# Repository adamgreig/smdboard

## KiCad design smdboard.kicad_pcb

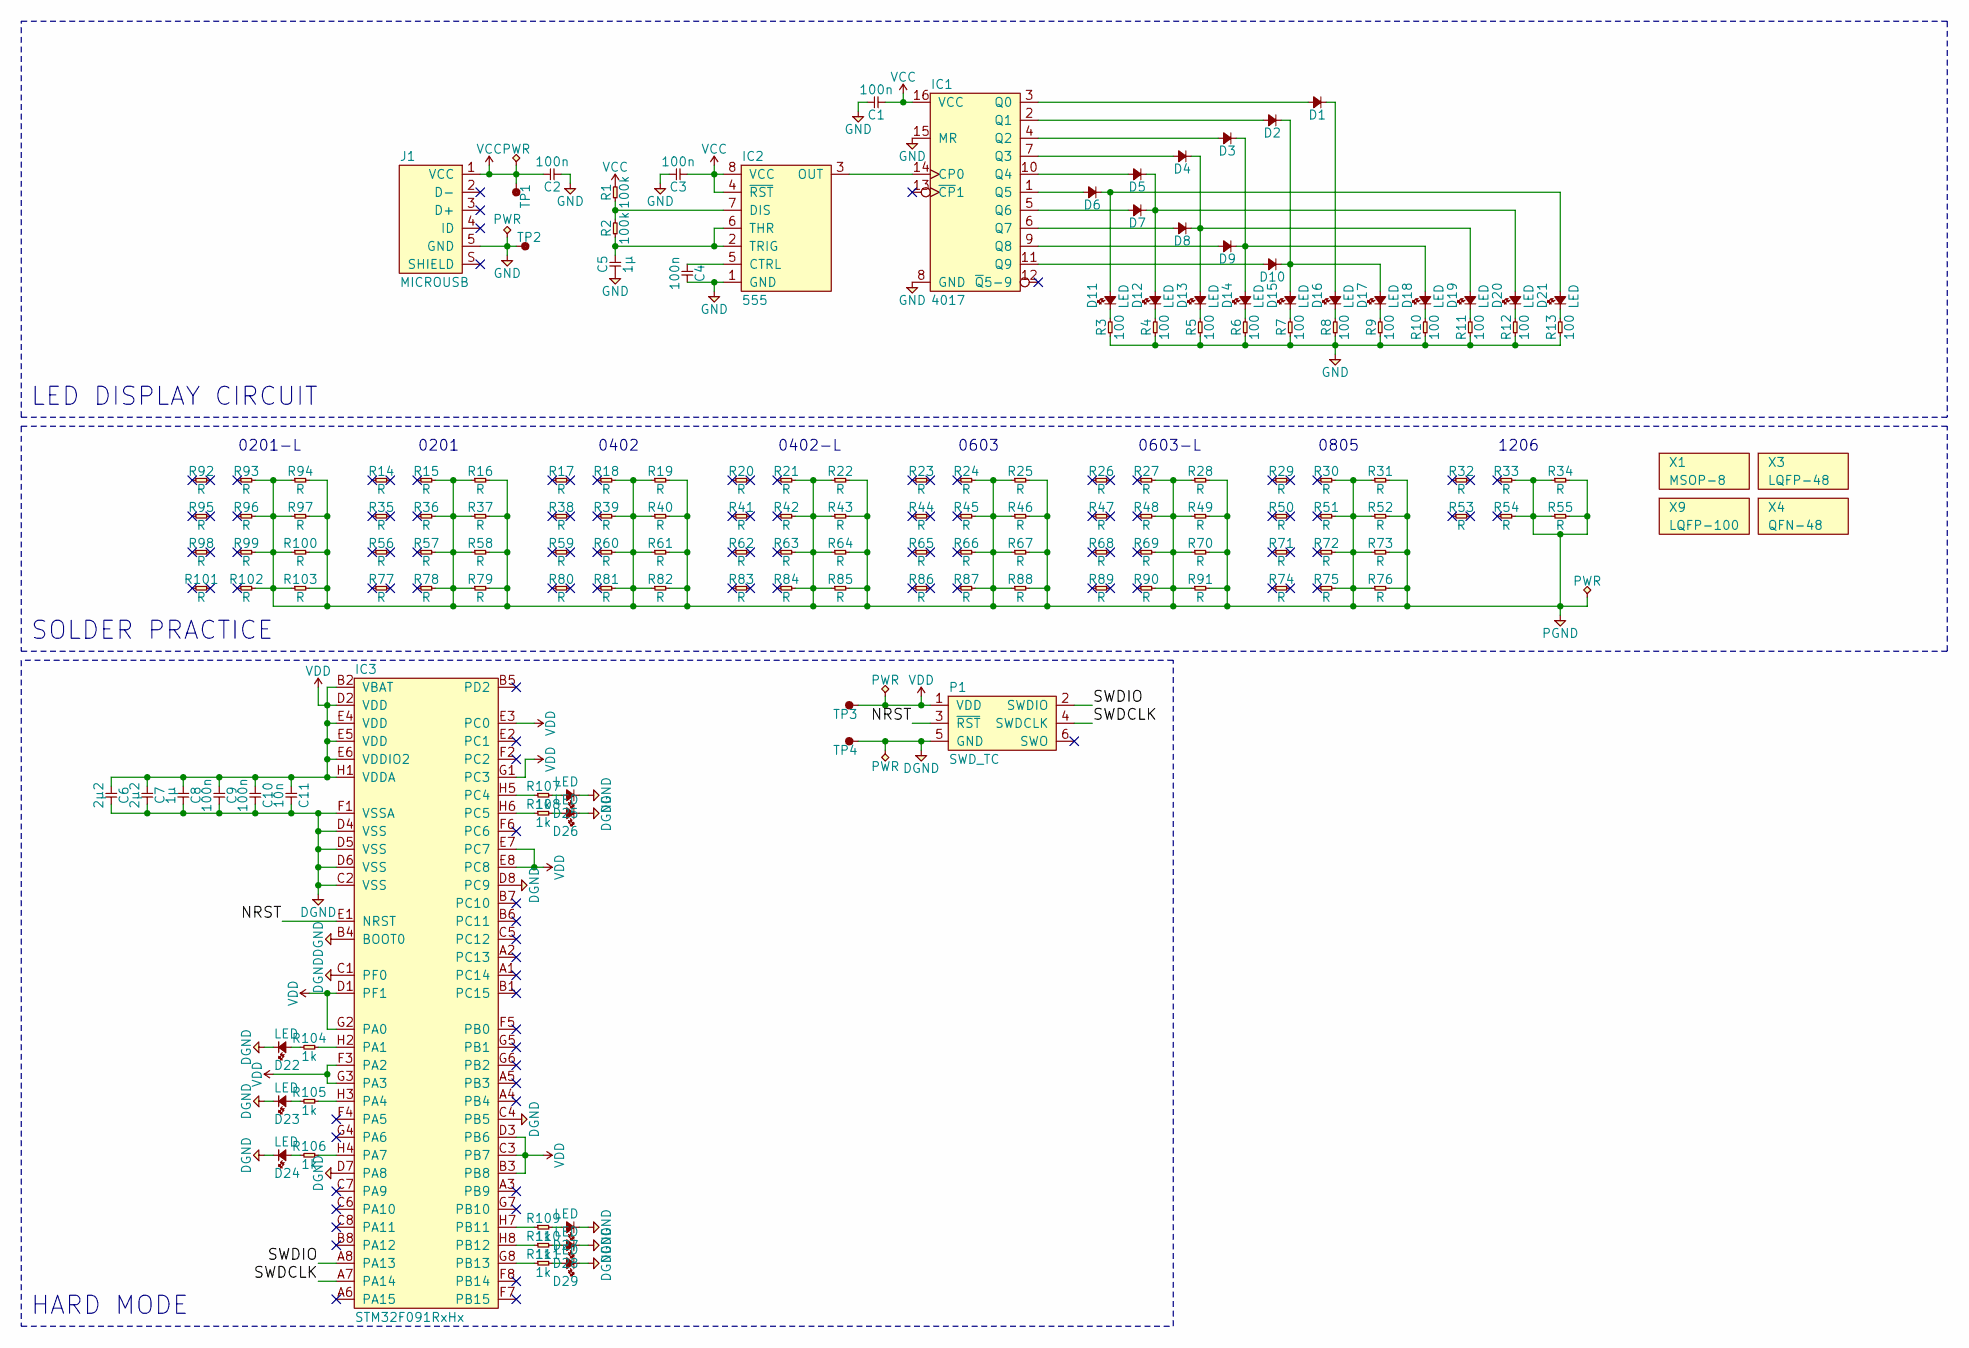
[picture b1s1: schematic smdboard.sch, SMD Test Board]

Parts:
C1, C2, C3, C4: 100n; 0805
C5: 1µ; 0805
C6, C7: 2µ2; 0603-L
C8: 1µ; 0603-L
C9, C10: 100n; 0402-L
C11: 10n; 0402-L
D1, D2, D3, D4, D5, D6, D7, D8, D9, D10: SOD-323; Farnell 1466524
D11, D12, D13, D14, D15, D16, D17, D18, D19, D20, D21: LED; 0805-LED
D22, D23, D24, D25, D26, D27, D28, D29: LED; 0603-LED
IC1: 4017; SOIC-16; Farnell 1085280
IC2: 555; SOIC-8; Farnell 9589880
IC3: STM32F091RxHx; UFBGA-64; Farnell 2503242
J1: MICROUSB; MICROUSB_MOLEX_47589-0001; Farnell 1568023
P1: SWD_TC; TC2030-NL
R1, R2: 100k; 0805
R3, R4, R5, R6, R7, R8, R9, R10, R11, R12, R13: 100; 0805
R14, R15, R16, R35, R36, R37, R56, R57, R58, R77, R78, R79: R; 0201
R17, R18, R19, R38, R39, R40, R59, R60, R61, R80, R81, R82: R; 0402
R20, R21, R22, R41, R42, R43, R62, R63, R64, R83, R84, R85: R; 0402-L
R23, R24, R25, R44, R45, R46, R65, R66, R67, R86, R87, R88: R; 0603
R26, R27, R28, R47, R48, R49, R68, R69, R70, R89, R90, R91: R; 0603-L
R29, R30, R31, R50, R51, R52, R71, R72, R73, R74, R75, R76: R; 0805
R32, R33, R34, R53, R54, R55: R; 1206
R92, R93, R94, R95, R96, R97, R98, R99, R100, R101, R102, R103: R; 0201-L
R104, R105, R106, R107, R108, R109, R110, R111: 1k; 0402-L
TP1, TP2, TP3, TP4: TESTPAD; WIREPAD
X1: MSOP-8
X3: LQFP-48
X4: QFN-48; QFN-48-EP-ST
X9: LQFP-100

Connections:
/NRST: IC3.E1 (NRST), P1.3 (~RST)
/SWDCLK: IC3.A7 (PA14), P1.4 (SWDCLK)
/SWDIO: IC3.A8 (PA13), P1.2 (SWDIO)
DGND: C6.2, C7.2, C8.2, C9.2, C10.2, C11.2, D22.1, D23.1, D24.1, D25.1, D26.1, D27.1, D28.1, D29.1, IC3.B4 (BOOT0), IC3.C1 (PF0), IC3.C2 (VSS), IC3.C4 (PB5), IC3.D4 (VSS), IC3.D5 (VSS), IC3.D6 (VSS), IC3.D7 (PA8), IC3.D8 (PC9), IC3.F1 (VSSA), P1.5 (GND), TP4.1
GND: C1.2, C2.1, C3.2, C4.2, C5.1, IC1.8 (GND), IC1.15 (MR), IC2.1 (GND), J1.5 (GND), R3.1, R4.1, R5.1, R6.1, R7.1, R8.1, R9.1, R10.1, R11.1, R12.1, R13.1, TP2.1
unnamed: C4.1, IC2.5 (CTRL)
unnamed: C5.2, IC2.2 (TRIG), IC2.6 (THR), R2.1
unnamed: D1.1, D16.2
unnamed: D1.2, IC1.3 (Q0)
unnamed: D2.2, IC1.2 (Q1)
unnamed: D3.2, IC1.4 (Q2)
unnamed: D4.2, IC1.7 (Q3)
unnamed: D5.2, IC1.10 (Q4)
unnamed: D6.2, IC1.1 (Q5)
unnamed: D7.2, IC1.5 (Q6)
unnamed: D8.2, IC1.6 (Q7)
unnamed: D9.2, IC1.9 (Q8)
unnamed: D2.1, D10.1, D15.2, D17.2
unnamed: D10.2, IC1.11 (Q9)
unnamed: D11.1, R3.2
unnamed: D6.1, D11.2, D21.2
unnamed: D12.1, R4.2
unnamed: D5.1, D7.1, D12.2, D20.2
unnamed: D13.1, R5.2
unnamed: D4.1, D8.1, D13.2, D19.2
unnamed: D14.1, R6.2
unnamed: D3.1, D9.1, D14.2, D18.2
unnamed: D15.1, R7.2
unnamed: D16.1, R8.2
unnamed: D17.1, R9.2
unnamed: D18.1, R10.2
unnamed: D19.1, R11.2
unnamed: D20.1, R12.2
unnamed: D21.1, R13.2
unnamed: D22.2, R104.2
unnamed: D23.2, R105.2
unnamed: D24.2, R106.2
unnamed: D25.2, R107.2
unnamed: D26.2, R108.2
unnamed: D27.2, R109.2
unnamed: D28.2, R110.2
unnamed: D29.2, R111.2
unnamed: IC1.14 (CP0), IC2.3 (OUT)
unnamed: IC2.7 (DIS), R1.1, R2.2
unnamed: IC3.G8 (PB13), R111.1
unnamed: IC3.H2 (PA1), R104.1
unnamed: IC3.H3 (PA4), R105.1
unnamed: IC3.H4 (PA7), R106.1
unnamed: IC3.H5 (PC4), R107.1
unnamed: IC3.H6 (PC5), R108.1
unnamed: IC3.H7 (PB11), R109.1
unnamed: IC3.H8 (PB12), R110.1
PGND: R15.2, R16.1, R16.2, R18.2, R19.1, R19.2, R21.2, R22.1, R22.2, R24.2, R25.1, R25.2, R27.2, R28.1, R28.2, R30.2, R31.1, R31.2, R33.2, R34.1, R34.2, R36.2, R37.1, R37.2, R39.2, R40.1, R40.2, R42.2, R43.1, R43.2, R45.2, R46.1, R46.2, R48.2, R49.1, R49.2, R51.2, R52.1, R52.2, R54.2, R55.1, R55.2, R57.2, R58.1, R58.2, R60.2, R61.1, R61.2, R63.2, R64.1, R64.2, R66.2, R67.1, R67.2, R69.2, R70.1, R70.2, R72.2, R73.1, R73.2, R75.2, R76.1, R76.2, R78.2, R79.1, R79.2, R81.2, R82.1, R82.2, R84.2, R85.1, R85.2, R87.2, R88.1, R88.2, R90.2, R91.1, R91.2, R93.2, R94.1, R94.2, R96.2, R97.1, R97.2, R99.2, R100.1, R100.2, R102.2, R103.1, R103.2
VCC: C1.1, C2.2, C3.1, IC1.16 (VCC), IC2.4 (~RST), IC2.8 (VCC), J1.1 (VCC), R1.2, TP1.1
VDD: C6.1, C7.1, C8.1, C9.1, C10.1, C11.1, IC3.B2 (VBAT), IC3.B3 (PB8), IC3.C3 (PB7), IC3.D1 (PF1), IC3.D2 (VDD), IC3.D3 (PB6), IC3.E3 (PC0), IC3.E4 (VDD), IC3.E5 (VDD), IC3.E6 (VDDIO2), IC3.E7 (PC7), IC3.E8 (PC8), IC3.F3 (PA2), IC3.G1 (PC3), IC3.G2 (PA0), IC3.G3 (PA3), IC3.H1 (VDDA), P1.1 (VDD), TP3.1

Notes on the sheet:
LED DISPLAY CIRCUIT
0201
0402
0402-L
0603
0603-L
0805
1206
0201-L
SOLDER PRACTICE
HARD MODE

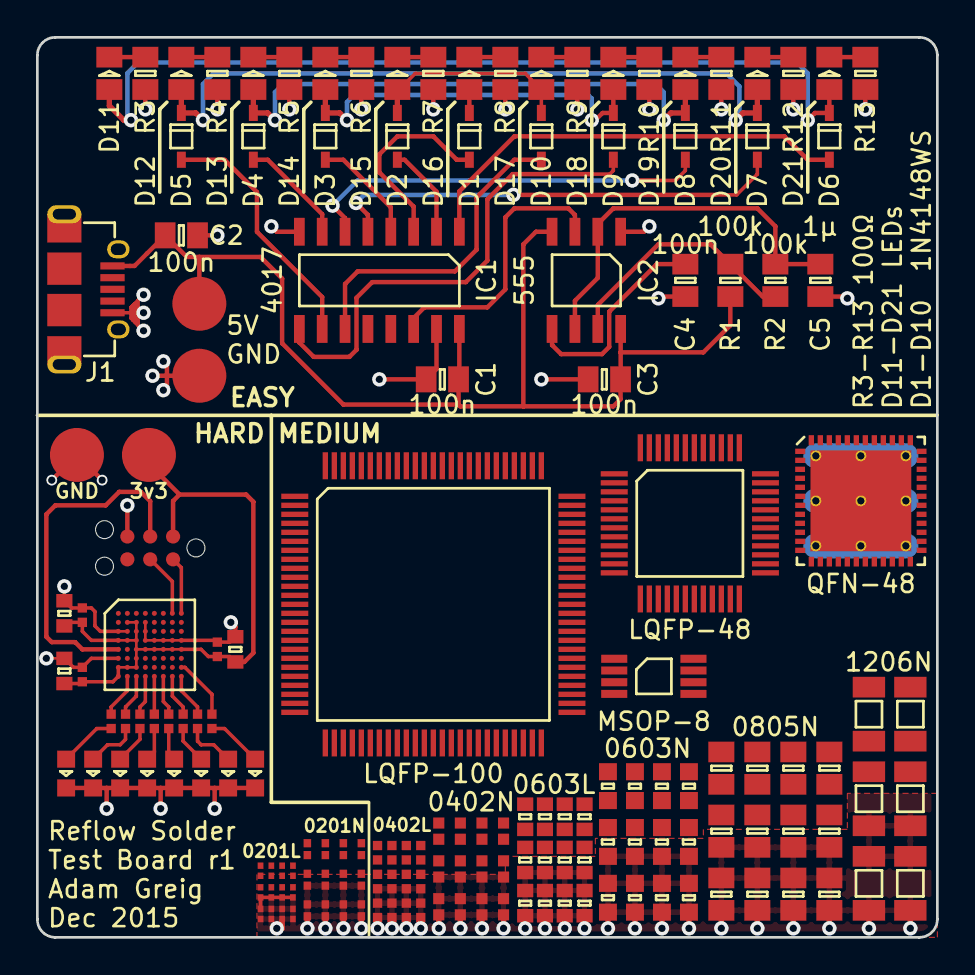
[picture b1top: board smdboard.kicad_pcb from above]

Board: 2 copper layers, 50.0 x 50.0 mm, 164 parts (0 on the bottom side), 55 nets.

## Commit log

2015-12-26 Draw LED circuit
2015-12-31 add first revision
2016-01-03 Update USB and QFN-48 parts. Redraw gerbers.
2016-01-03 Add zip for manufacturing
2016-01-03 Add Farnell order codes
2016-01-23 add basic firmware for bga part
2016-01-23 add paste dxf
2016-01-24 enable gpio clocks properly
